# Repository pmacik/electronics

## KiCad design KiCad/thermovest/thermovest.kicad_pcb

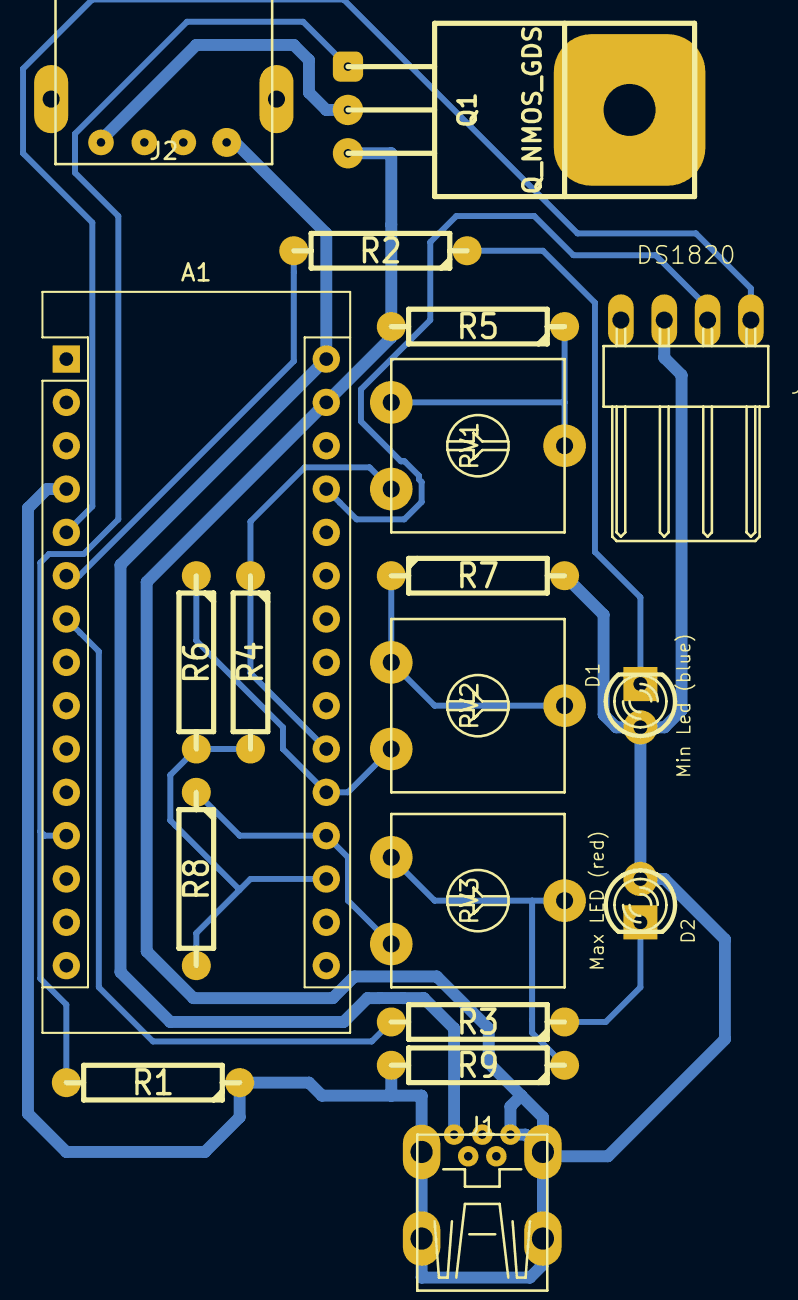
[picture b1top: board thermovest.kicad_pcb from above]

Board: 2 copper layers, 19 parts (0 on the bottom side), 17 nets.

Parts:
A1: Arduino_Nano_v3.x; Arduino_Nano
D1: Min Led (blue); LED-3MM-Large-pads
D2: Max LED (red); LED-3MM-Large-pads
J1: Power In; USB-mini
J2: Thermo Out; USB-A
J3: DS1820; PINHEAD1-4-90
Q1: Q_NMOS_GDS; TO220-123
R1, R2, R3: 1k; R4_LARGE_PADS
R4, R5, R6, R7, R8, R9: 220R; R4_LARGE_PADS
RV1: Requested Temp (4k7); Trimr
RV2: Min Temp (1k); Trimr
RV3: Max Temp (1k); Trimr

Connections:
GND: A1.4, A1.29, D1.1, D2.1, J1.5, J1.6, J3.3, Q1.3, R1.1, R5.2, R7.2, R9.2
unnamed: A1.5, J3.1
unnamed: A1.6, R2.2
unnamed: A1.7, R3.2
unnamed: A1.12, Q1.1, R1.2
unnamed: A1.18, R4.2, R6.2, R8.2
unnamed: A1.19, R8.1, RV3.3
unnamed: A1.20, R6.1, RV2.3
unnamed: A1.21, R4.1, RV1.3
unnamed: A1.27, J3.2
unnamed: A1.30, J1.1, J2.1
unnamed: D1.2, R2.1
unnamed: D2.2, R3.1
unnamed: J2.4, Q1.2
unnamed: R5.1, RV1.1, RV1.2
unnamed: R7.1, RV2.1, RV2.2
unnamed: R9.1, RV3.1, RV3.2

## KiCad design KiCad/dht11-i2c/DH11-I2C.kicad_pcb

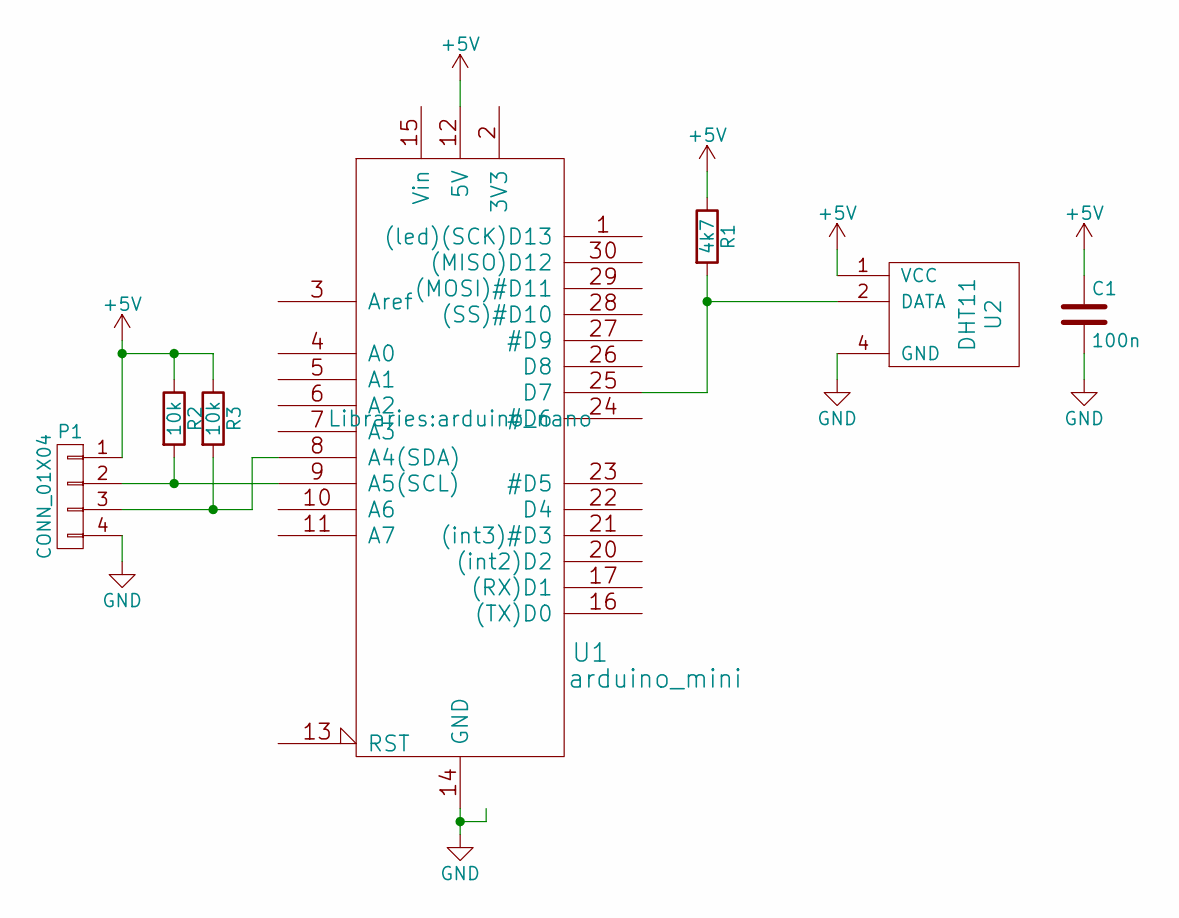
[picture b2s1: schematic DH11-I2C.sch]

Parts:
C1: 100n; C2
P1: CONN_01X04; Pin_Header_Angled_1x04
R1: 4k7; R3-LARGE_PADS
R2, R3: 10k; R3-LARGE_PADS
U1: arduino_mini; arduino_nano
U2: DHT11; Pin_Header_Angled_1x04

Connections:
+5V: C1.1, P1.1, R1.1, R2.1, R3.1, U1.12 (5V), U2.1 (VCC)
GND: C1.2, P1.4, U1.14 (GND), U1.19 (GND), U2.4 (GND)
unnamed: P1.2, R2.2, U1.9 (A5(SCL))
unnamed: P1.3, R3.2, U1.8 (A4(SDA))
unnamed: R1.2, U1.25 (D7), U2.2 (DATA)

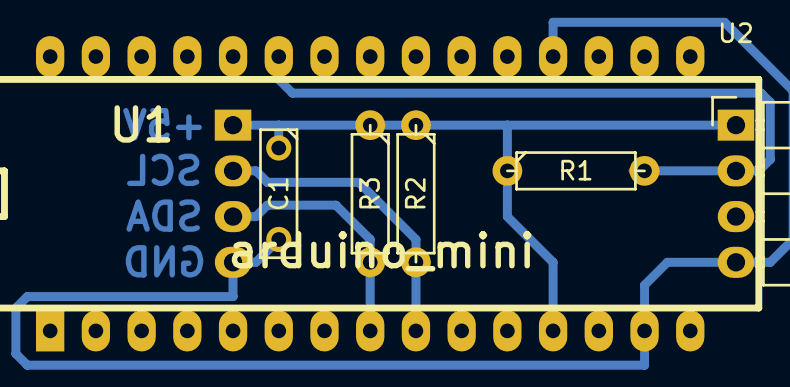
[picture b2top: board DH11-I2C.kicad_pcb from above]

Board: 2 copper layers, 7 parts (1 on the bottom side), 5 nets.

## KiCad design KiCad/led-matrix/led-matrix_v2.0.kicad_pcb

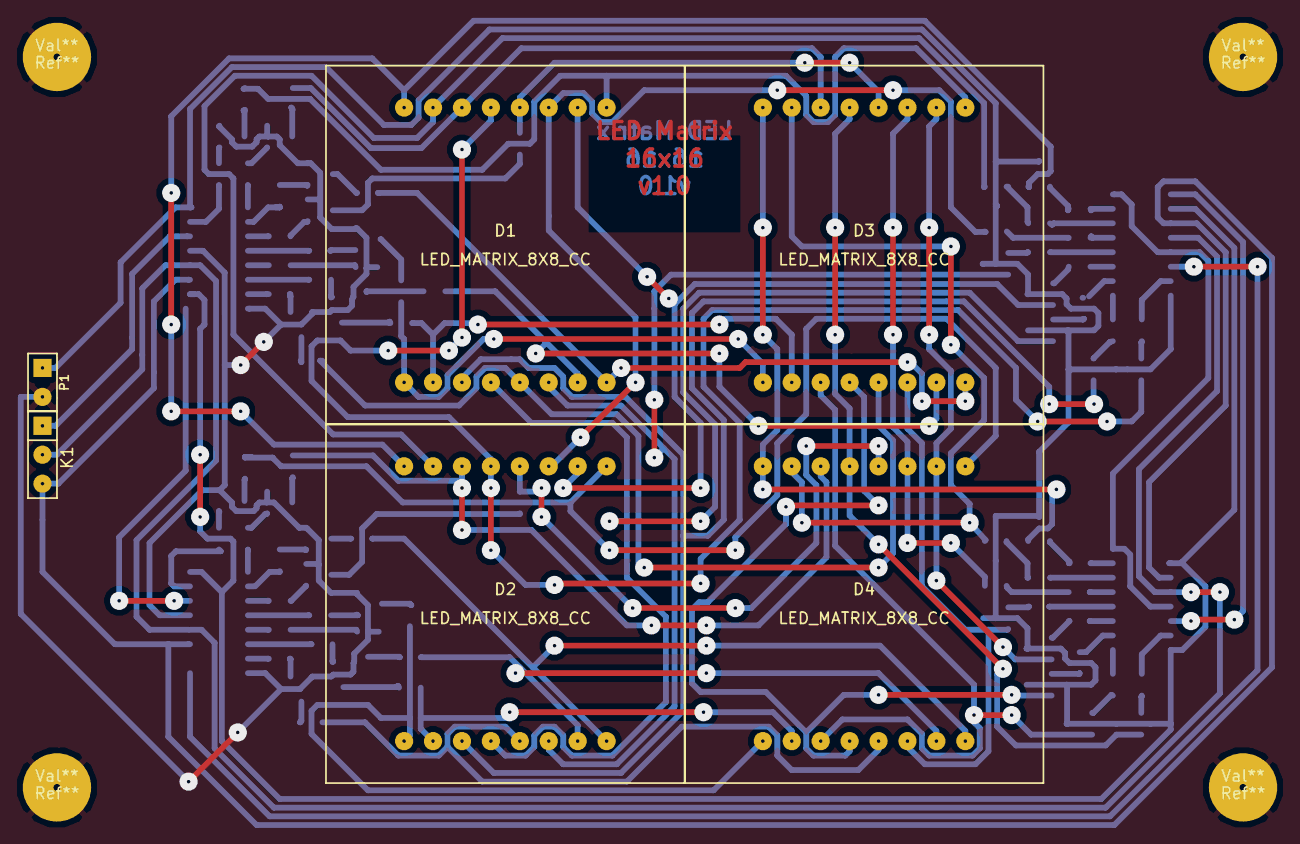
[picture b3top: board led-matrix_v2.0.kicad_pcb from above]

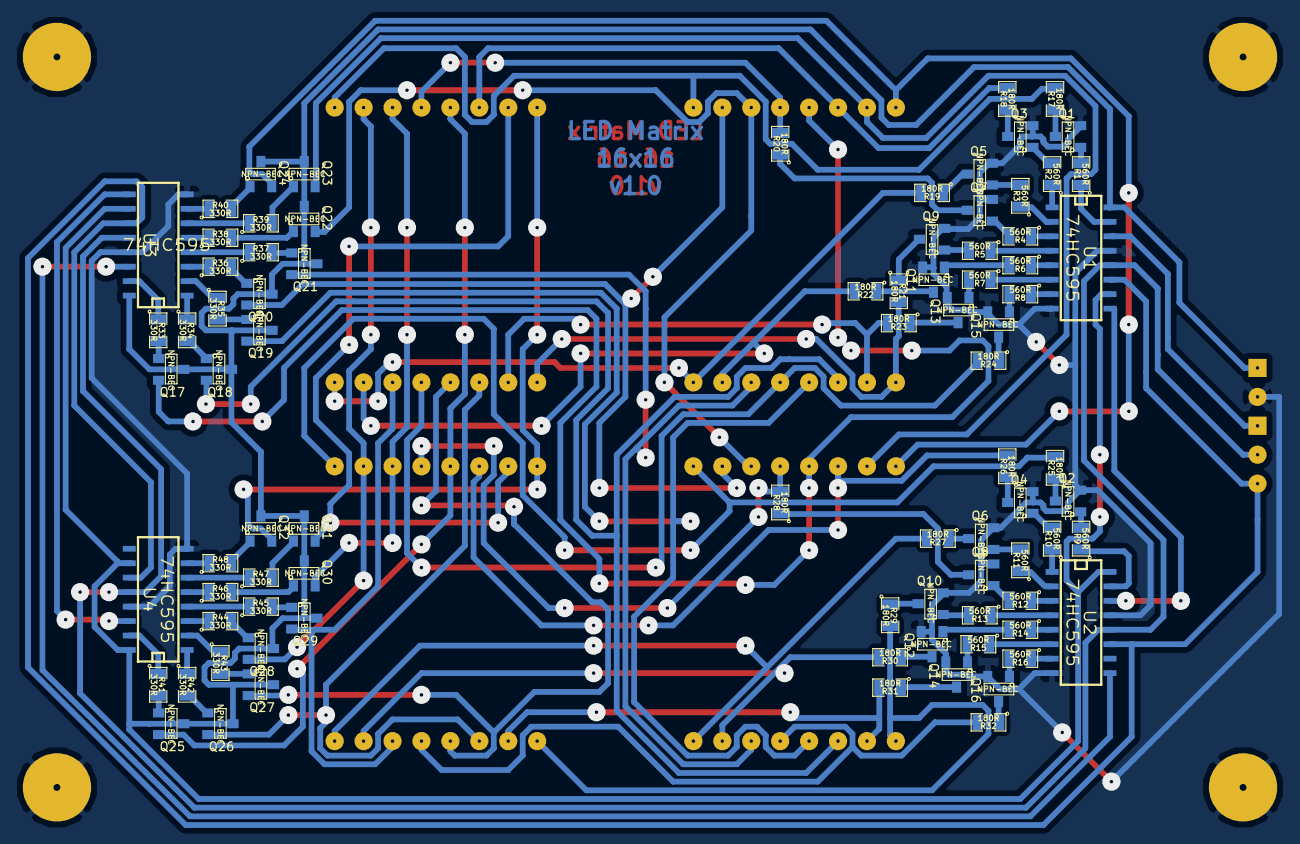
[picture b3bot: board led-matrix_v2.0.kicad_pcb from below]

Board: 2 copper layers, 94 parts (84 on the bottom side), 120 nets.

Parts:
D1, D2, D3, D4: LED_MATRIX_8X8_CC; LED_MATRIX_8x8
K1: CONN_3; PIN_ARRAY_3X1
P1: CONN_2; PIN_ARRAY_2X1
Q1, Q2, Q3, Q4, Q5, Q6, Q7, Q8, Q9, Q10, Q11, Q12, Q13, Q14, Q15, Q16, Q17, Q18, Q19, Q20, Q21, Q22, Q23, Q24, Q25, Q26, Q27, Q28, Q29, Q30, Q31, Q32: NPN-BEC; SOT23
R1, R2, R3, R4, R5, R6, R7, R8, R9, R10, R11, R12, R13, R14, R15, R16: 560R; SM0805
R17, R18, R19, R20, R21, R22, R23, R24, R25, R26, R27, R28, R29, R30, R31, R32: 180R; SM0805
R33, R34, R35, R36, R37, R38, R39, R40, R41, R42, R43, R44, R45, R46, R47, R48: 330R; SM0805
Ref**: Val**; pad
Ref**#2, Ref**#3, Ref**#4: Val**; pad
U1, U2, U3, U4: 74HC595; SO16E

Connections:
GND: P1.2, Q1.2, Q2.2, Q3.2, Q4.2, Q5.2, Q6.2, Q7.2, Q8.2, Q9.2, Q10.2, Q11.2, Q12.2, Q13.2, Q14.2, Q15.2, Q16.2, U1.8, U1.13, U2.8, U2.13, U3.8, U3.13, U4.8, U4.13
unnamed: R42.1, U4.1
unnamed: R43.1, U4.2
unnamed: R44.1, U4.3
unnamed: D3.11, D4.11, Q30.2
unnamed: Q29.1, R45.2
unnamed: Q30.1, R46.2
unnamed: R45.1, U4.4
unnamed: Q31.1, R47.2
unnamed: Q32.1, R48.2
unnamed: R14.1, U2.5
unnamed: R3.1, U1.2
unnamed: R4.1, U1.3
unnamed: R5.1, U1.4
unnamed: R6.1, U1.5
unnamed: R7.1, U1.6
unnamed: R8.1, U1.7
unnamed: R9.1, U2.15
unnamed: R10.1, U2.1
unnamed: R11.1, U2.2
unnamed: R12.1, U2.3
unnamed: R13.1, U2.4
unnamed: R2.1, U1.1
unnamed: R15.1, U2.6
unnamed: R16.1, U2.7
unnamed: Q14.1, R15.2
unnamed: R46.1, U4.5
unnamed: R47.1, U4.6
unnamed: R48.1, U4.7
unnamed: U3.9, U4.14
unnamed: R1.1, U1.15
unnamed: Q2.1, R9.2
unnamed: Q12.1, R14.2
unnamed: Q16.1, R16.2
unnamed: Q10.1, R13.2
unnamed: Q8.1, R12.2
unnamed: Q6.1, R11.2
unnamed: Q4.1, R10.2
unnamed: Q19.1, R35.2
unnamed: Q20.1, R36.2
unnamed: Q21.1, R37.2
unnamed: D1.11, D2.11, Q22.2
unnamed: Q23.1, R39.2
unnamed: Q24.1, R40.2
unnamed: Q5.1, R3.2
unnamed: Q15.1, R8.2
unnamed: Q13.1, R7.2
unnamed: Q11.1, R6.2
unnamed: Q9.1, R5.2
unnamed: Q7.1, R4.2
unnamed: Q3.1, R2.2
unnamed: Q1.1, R1.2
unnamed: Q18.1, R34.2
unnamed: K1.1, U1.14
unnamed: U2.9, U3.14
unnamed: U1.9, U2.14
unnamed: K1.2, U1.12, U2.12, U3.12, U4.12
unnamed: R33.1, U3.15
unnamed: Q22.1, R38.2
unnamed: Q17.1, R33.2
unnamed: K1.3, U1.11, U2.11, U3.11, U4.11
unnamed: R38.1, U3.5
unnamed: Q7.3, R20.1
unnamed: D2.1, D4.1, R29.2
unnamed: D2.2, D4.2, R31.2
unnamed: Q3.3, R18.1
unnamed: Q5.3, R19.1
unnamed: R34.1, U3.1
unnamed: R35.1, U3.2
unnamed: R36.1, U3.3
unnamed: R37.1, U3.4
unnamed: R39.1, U3.6
unnamed: R40.1, U3.7
unnamed: R41.1, U4.15
unnamed: Q25.1, R41.2
unnamed: Q26.1, R42.2
unnamed: Q27.1, R43.2
unnamed: Q28.1, R44.2
unnamed: D2.5, D4.5, R32.2
unnamed: D1.15, D2.15, Q23.2
unnamed: D2.14, D4.14, R26.2
unnamed: D1.16, D2.16, Q24.2
unnamed: D2.9, D4.9, R25.2
unnamed: D1.14, D3.14, R18.2
unnamed: D1.8, D3.8, R19.2
unnamed: D2.7, D4.7, R30.2
unnamed: D2.12, D4.12, R28.2
unnamed: D2.8, D4.8, R27.2
unnamed: D3.15, D4.15, Q31.2
unnamed: D3.10, D4.10, Q28.2
unnamed: D3.13, D4.13, Q25.2
unnamed: D3.16, D4.16, Q32.2
unnamed: D3.6, D4.6, Q29.2
unnamed: D1.2, D3.2, R23.2
unnamed: D1.5, D3.5, R24.2
unnamed: D3.3, D4.3, Q26.2
unnamed: D3.4, D4.4, Q27.2
unnamed: D1.13, D2.13, Q17.2
unnamed: D1.3, D2.3, Q18.2
unnamed: D1.4, D2.4, Q19.2
unnamed: D1.6, D2.6, Q21.2
unnamed: D1.10, D2.10, Q20.2
unnamed: Q8.3, R28.1
unnamed: Q6.3, R27.1
unnamed: Q4.3, R26.1
unnamed: Q2.3, R25.1
unnamed: Q15.3, R24.1
unnamed: Q13.3, R23.1
unnamed: Q11.3, R22.1
unnamed: Q9.3, R21.1
unnamed: Q1.3, R17.1
unnamed: D1.9, D3.9, R17.2
unnamed: Q16.3, R32.1
unnamed: Q14.3, R31.1
unnamed: Q12.3, R30.1
unnamed: Q10.3, R29.1
unnamed: D1.12, D3.12, R20.2
unnamed: D1.7, D3.7, R22.2
unnamed: D1.1, D3.1, R21.2
VCC: P1.1, Q17.3, Q18.3, Q19.3, Q20.3, Q21.3, Q22.3, Q23.3, Q24.3, Q25.3, Q26.3, Q27.3, Q28.3, Q29.3, Q30.3, Q31.3, Q32.3, U1.10, U1.16, U2.10, U2.16, U3.10, U3.16, U4.10, U4.16

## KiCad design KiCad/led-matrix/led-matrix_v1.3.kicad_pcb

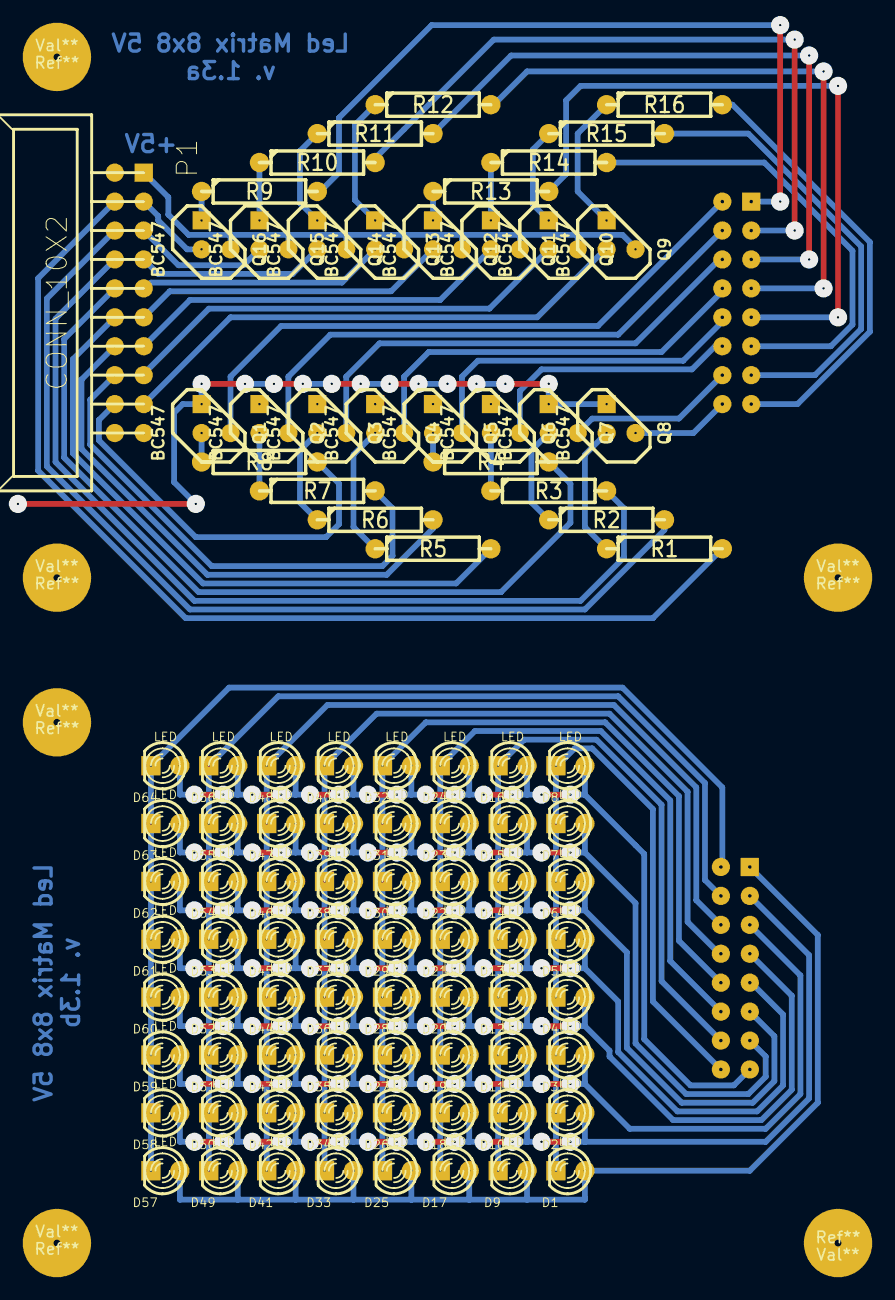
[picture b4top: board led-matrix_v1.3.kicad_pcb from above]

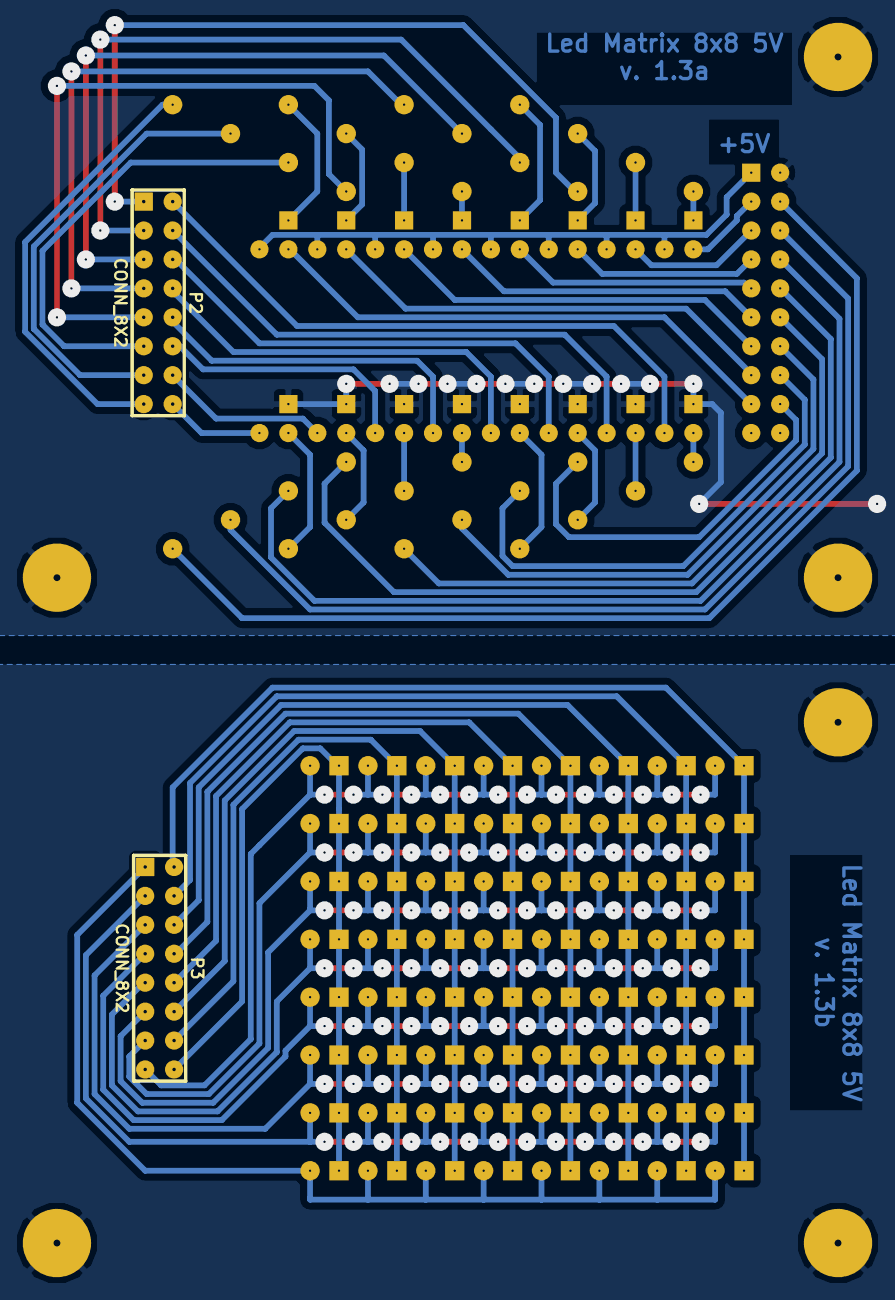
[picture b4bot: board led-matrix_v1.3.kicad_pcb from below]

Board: 2 copper layers, 105 parts (2 on the bottom side), 66 nets.

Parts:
D1, D2, D3, D4, D5, D6, D7, D8, D9, D10, D11, D12, D13, D14, D15, D16, D17, D18, D19, D20, D21, D22, D23, D24, D25, D26, D27, D28, D29, D30, D31, D32, D33, D34, D35, D36, D37, D38, D39, D40, D41, D42, D43, D44, D45, D46, D47, D48, D49, D50, D51, D52, D53, D54, D55, D56, D57, D58, D59, D60, D61, D62, D63, D64: LED; LED_3MM
P1: CONN_10X2; VASCH10x2_90
P2, P3: CONN_8X2; pin_array_8x2_large
Q1, Q2, Q3, Q4, Q5, Q6, Q7, Q8, Q9, Q10, Q11, Q12, Q13, Q14, Q15, Q16: BC547; TO92_123
R1, R2, R3, R4, R5, R6, R7, R8, R9, R10, R11, R12, R13, R14, R15, R16: R; R4_LARGE_PADS
Ref**: Val**; pad
Ref**#2, Ref**#3, Ref**#4, Ref**#5, Ref**#6: Val**; pad

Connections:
GND: P1.1, Q1.3, Q2.3, Q3.3, Q4.3, Q5.3, Q6.3, Q7.3, Q8.3
unnamed: P1.18, Q9.2
unnamed: Q13.3, R12.1
unnamed: Q12.3, R13.1
unnamed: P1.14, Q11.2
unnamed: Q11.3, R14.1
unnamed: P1.16, Q10.2
unnamed: Q10.3, R15.1
unnamed: P1.10, Q13.2
unnamed: Q9.3, R16.1
unnamed: Q16.3, R9.1
unnamed: Q15.3, R10.1
unnamed: Q14.3, R11.1
unnamed: Q5.2, R4.1
unnamed: Q6.2, R3.1
unnamed: Q7.2, R2.1
unnamed: Q8.2, R1.1
unnamed: P1.4, Q16.2
unnamed: P1.6, Q15.2
unnamed: P1.8, Q14.2
unnamed: P1.12, Q12.2
unnamed: Q2.2, R7.1
unnamed: P2.10, Q5.1
unnamed: P2.6, Q3.1
unnamed: Q3.2, R6.1
unnamed: P2.16, Q8.1
unnamed: P2.4, Q2.1
unnamed: P2.8, Q4.1
unnamed: Q4.2, R5.1
unnamed: P2.2, Q1.1
unnamed: Q1.2, R8.1
unnamed: P2.14, Q7.1
unnamed: P2.12, Q6.1
unnamed: P1.5, R2.2
unnamed: P1.7, R3.2
unnamed: P1.9, R4.2
unnamed: P1.11, R5.2
unnamed: P1.13, R6.2
unnamed: P1.15, R7.2
unnamed: P1.17, R8.2
unnamed: P1.3, R1.2
unnamed: P2.1, R9.2
unnamed: P2.3, R10.2
unnamed: P2.5, R11.2
unnamed: P2.7, R12.2
unnamed: P2.9, R13.2
unnamed: P2.11, R14.2
unnamed: P2.15, R16.2
unnamed: P2.13, R15.2
unnamed: D4.1, D12.1, D20.1, D28.1, D36.1, D44.1, D52.1, D60.1, P3.7
unnamed: D5.1, D13.1, D21.1, D29.1, D37.1, D45.1, D53.1, D61.1, P3.9
unnamed: D7.1, D15.1, D23.1, D31.1, D39.1, D47.1, D55.1, D63.1, P3.13
unnamed: D1.2, D2.2, D3.2, D4.2, D5.2, D6.2, D7.2, D8.2, P3.16
unnamed: D17.2, D18.2, D19.2, D20.2, D21.2, D22.2, D23.2, D24.2, P3.12
unnamed: D9.2, D10.2, D11.2, D12.2, D13.2, D14.2, D15.2, D16.2, P3.14
unnamed: D1.1, D9.1, D17.1, D25.1, D33.1, D41.1, D49.1, D57.1, P3.1
unnamed: D3.1, D11.1, D19.1, D27.1, D35.1, D43.1, D51.1, D59.1, P3.5
unnamed: D2.1, D10.1, D18.1, D26.1, D34.1, D42.1, D50.1, D58.1, P3.3
unnamed: D57.2, D58.2, D59.2, D60.2, D61.2, D62.2, D63.2, D64.2, P3.2
unnamed: D41.2, D42.2, D43.2, D44.2, D45.2, D46.2, D47.2, D48.2, P3.6
unnamed: D49.2, D50.2, D51.2, D52.2, D53.2, D54.2, D55.2, D56.2, P3.4
unnamed: D25.2, D26.2, D27.2, D28.2, D29.2, D30.2, D31.2, D32.2, P3.10
unnamed: D8.1, D16.1, D24.1, D32.1, D40.1, D48.1, D56.1, D64.1, P3.15
unnamed: D33.2, D34.2, D35.2, D36.2, D37.2, D38.2, D39.2, D40.2, P3.8
unnamed: D6.1, D14.1, D22.1, D30.1, D38.1, D46.1, D54.1, D62.1, P3.11
VCC: P1.2, Q9.1, Q10.1, Q11.1, Q12.1, Q13.1, Q14.1, Q15.1, Q16.1

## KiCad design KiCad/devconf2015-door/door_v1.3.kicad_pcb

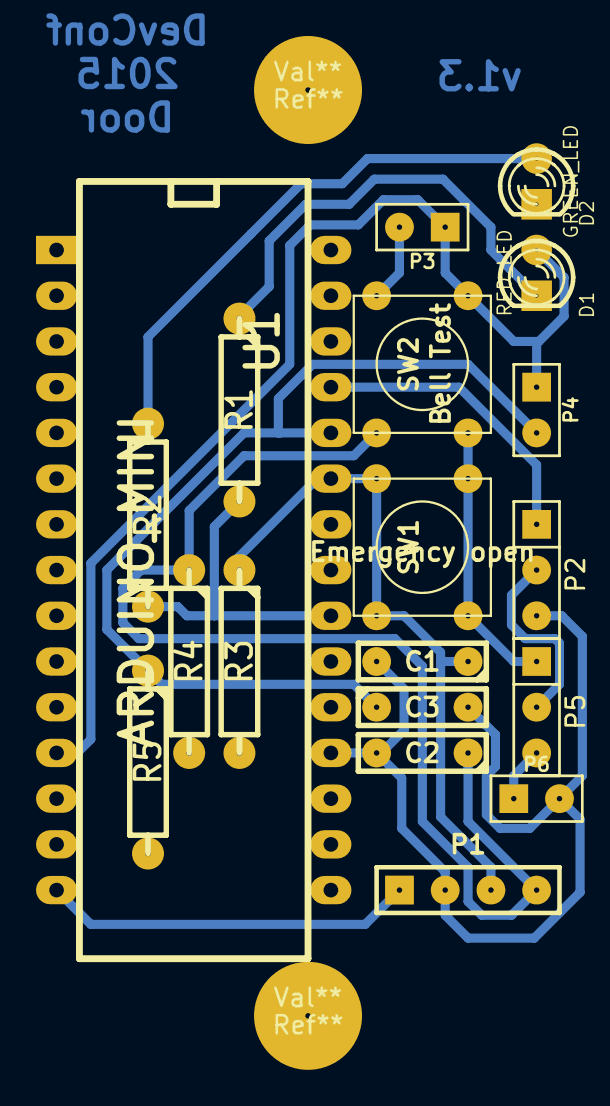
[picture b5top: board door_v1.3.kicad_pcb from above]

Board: 2 copper layers, 21 parts (0 on the bottom side), 12 nets.

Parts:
C1, C2, C3: 100nF; C2
D1: RED_LED; LED_3MM
D2: GREEN_LED; LED_3MM
P1: Cubieboard; PIN_ARRAY_4x1
P2: Servo; PIN_ARRAY_3X1
P3: Bell; PIN_ARRAY_2X1
P4: Door Open; PIN_ARRAY_2X1
P5: Servo PWR Jmpr; PIN_ARRAY_3X1
P6: Servo Ext PWR; PIN_ARRAY_2X1
R1, R2: R; R4-LARGE_PADS
R3, R4, R5: 1M; R4-LARGE_PADS
Ref**: Val**; pad
Ref**#2: Val**; pad
SW1: Emergency open; SW_PUSH_SMALL
SW2: Bell Test; SW_PUSH_SMALL
U1: ARDUINO_MINI; arduino_mini

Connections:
+5V: D1.1, P3.1, P4.1, P5.1, SW1.2, SW2.2, U1.12
GND: C1.2, C2.2, C3.2, D2.2, P1.2, P2.3, P6.2, R3.2, R4.2, R5.2, U1.14, U1.19
unnamed: R1.2, R2.1, U1.22
unnamed: D2.1, R2.2
unnamed: D1.2, R1.1
unnamed: P2.1, U1.27
unnamed: P5.3, P6.1
unnamed: P2.2, P5.2
unnamed: C3.1, P4.2, R5.1, U1.26
unnamed: C1.1, P1.3, R3.1, SW1.1, U1.25
unnamed: C2.1, P1.4, P3.2, R4.1, SW2.1
VCC: P1.1, U1.15

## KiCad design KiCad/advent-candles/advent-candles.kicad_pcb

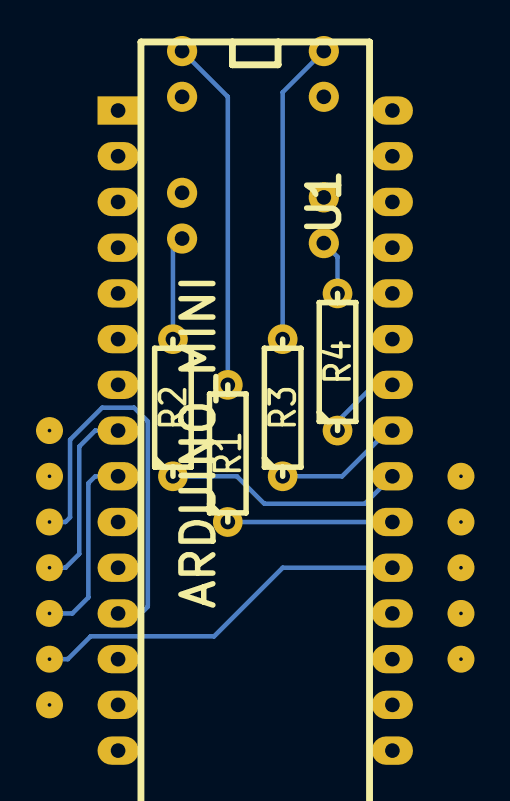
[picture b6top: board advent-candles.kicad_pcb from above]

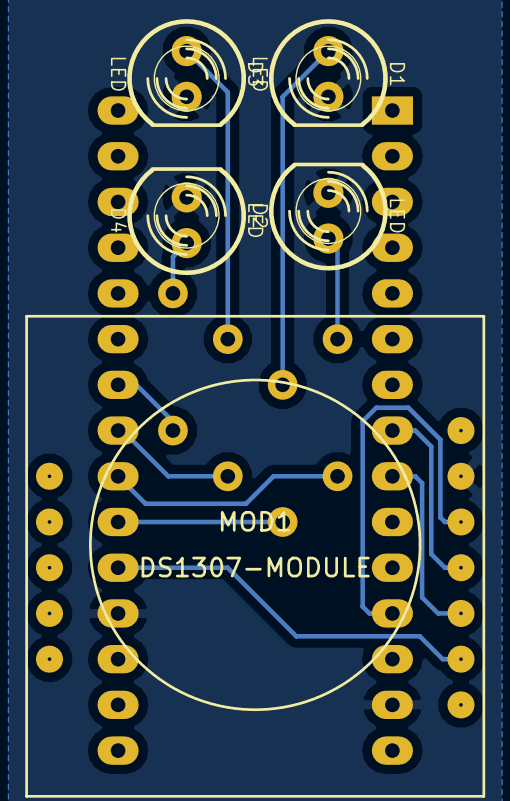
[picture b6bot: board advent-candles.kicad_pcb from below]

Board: 2 copper layers, 10 parts (5 on the bottom side), 13 nets.

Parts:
D1, D2, D3, D4: LED; LED-5MM
MOD1: DS1307-MODULE
R1, R2, R3, R4: R; R3-LARGE_PADS
U1: ARDUINO_MINI; arduino_mini

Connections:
GND: D1.2, D2.2, D3.2, D4.2, MOD1.6, U1.14, U1.19
unnamed: D3.1, R3.2
unnamed: D2.1, R2.2
unnamed: D1.1, R1.2
unnamed: D4.1, R4.2
unnamed: MOD1.5, U1.12
unnamed: MOD1.4, U1.8
unnamed: R4.1, U1.24
unnamed: R3.1, U1.23
unnamed: R2.1, U1.22
unnamed: R1.1, U1.21
unnamed: MOD1.3, U1.9
unnamed: MOD1.2, U1.20

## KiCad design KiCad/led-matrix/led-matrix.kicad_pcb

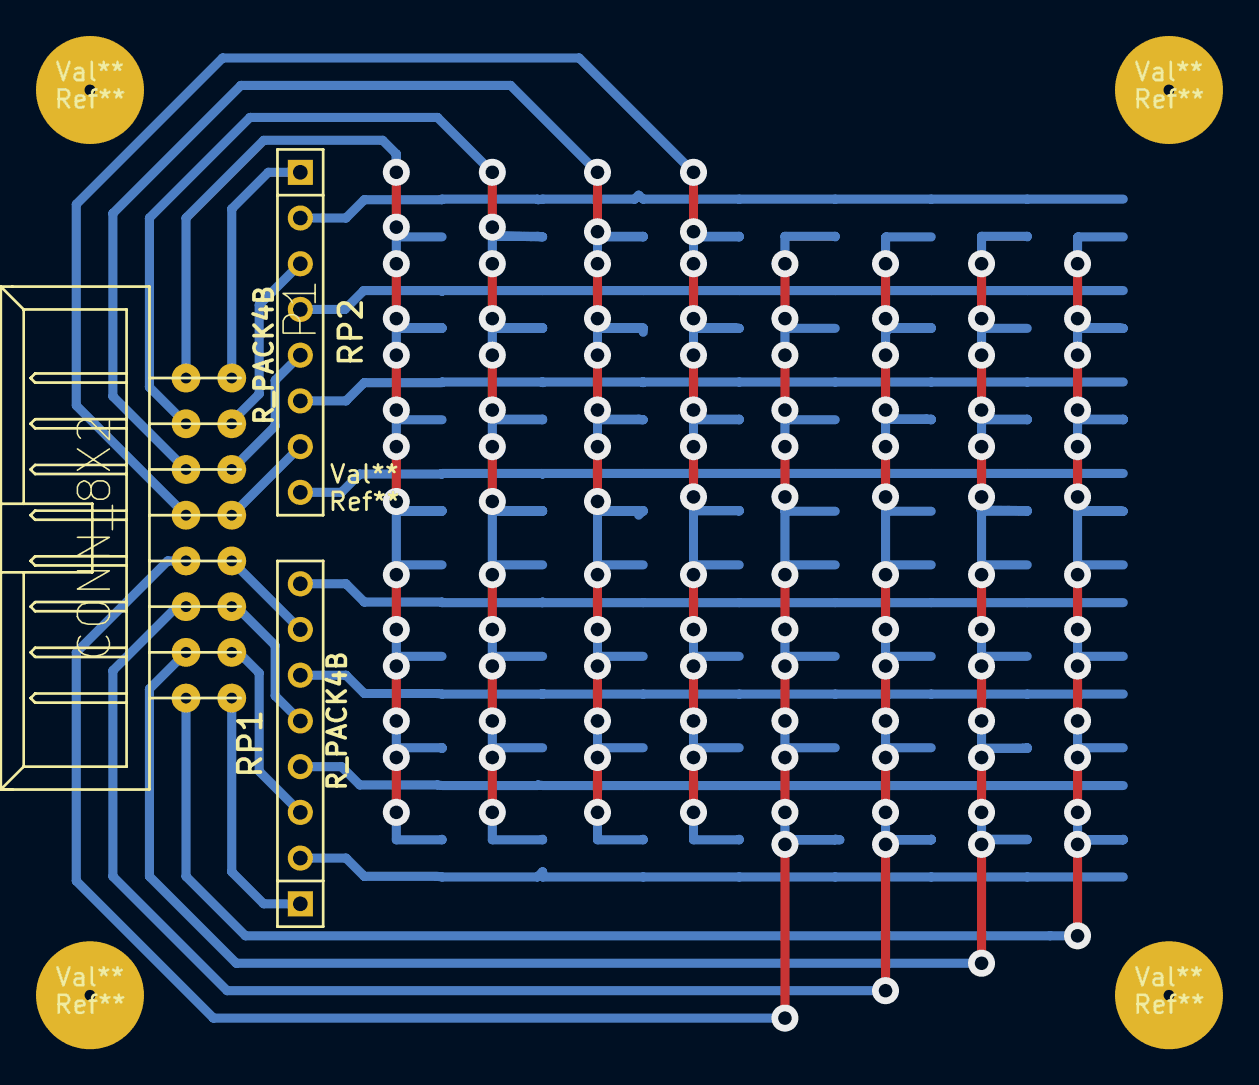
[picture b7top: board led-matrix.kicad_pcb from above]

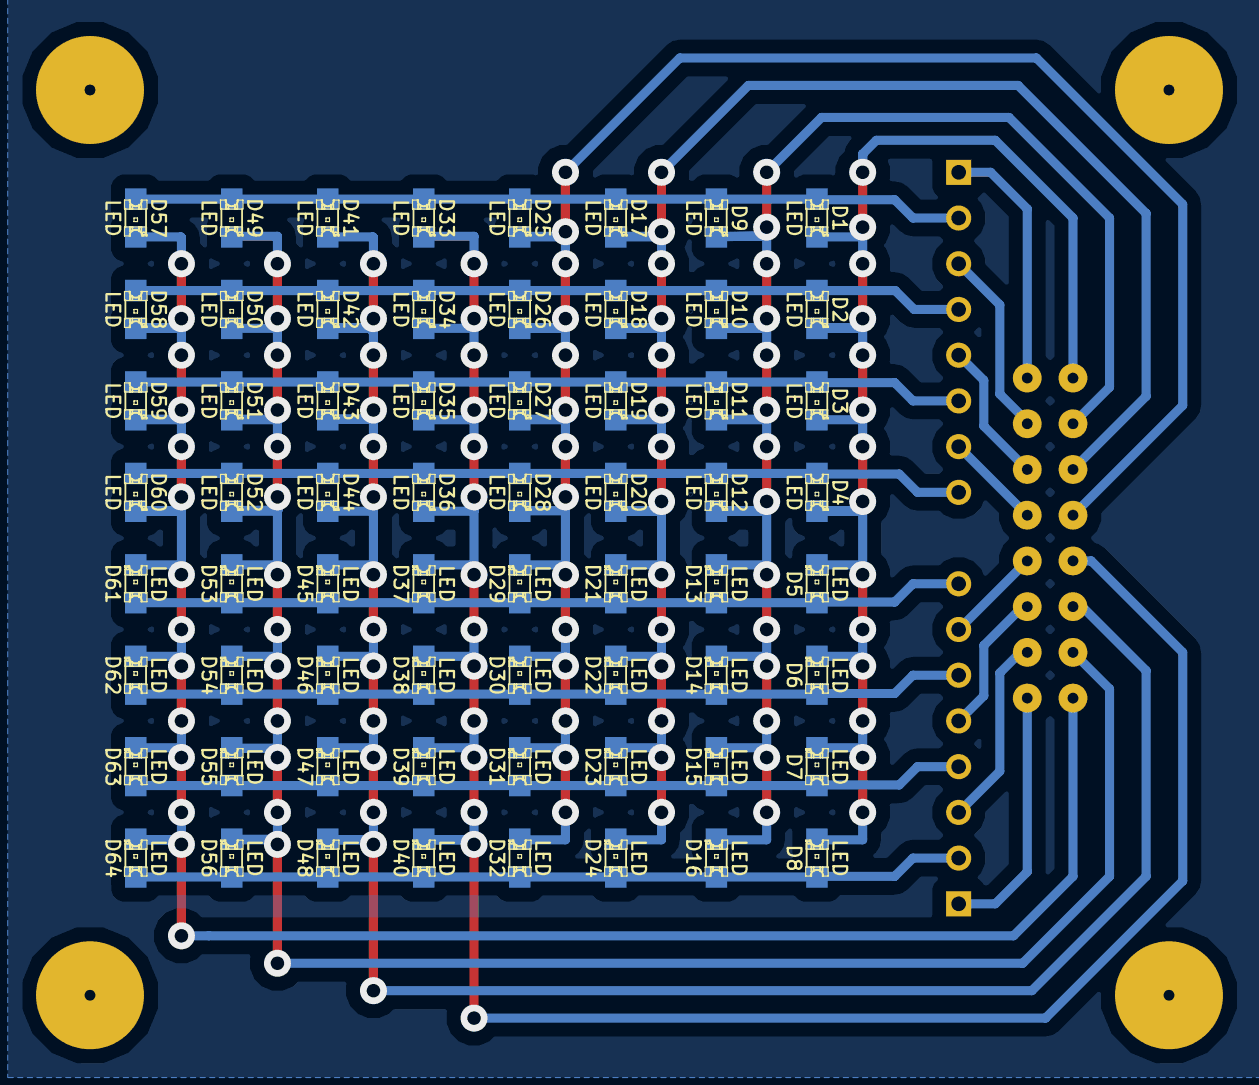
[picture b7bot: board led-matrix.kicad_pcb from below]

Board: 2 copper layers, 72 parts (64 on the bottom side), 24 nets.

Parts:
D1, D2, D3, D4, D5, D6, D7, D8, D9, D10, D11, D12, D13, D14, D15, D16, D17, D18, D19, D20, D21, D22, D23, D24, D25, D26, D27, D28, D29, D30, D31, D32, D33, D34, D35, D36, D37, D38, D39, D40, D41, D42, D43, D44, D45, D46, D47, D48, D49, D50, D51, D52, D53, D54, D55, D56, D57, D58, D59, D60, D61, D62, D63, D64: LED; LED-0805
P1: CONN_8X2; VASCH8x2-90
RP1, RP2: R_PACK4B; r_pack4B
Ref**: Val**; pad
Ref**#2, Ref**#3, Ref**#4, Ref**#5: Val**; pad

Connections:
unnamed: D17.2, D18.2, D19.2, D20.2, D21.2, D22.2, D23.2, D24.2, P1.5
unnamed: D9.2, D10.2, D11.2, D12.2, D13.2, D14.2, D15.2, D16.2, P1.3
unnamed: D1.2, D2.2, D3.2, D4.2, D5.2, D6.2, D7.2, D8.2, P1.1
unnamed: D8.1, D16.1, D24.1, D32.1, D40.1, D48.1, D56.1, D64.1, RP1.2
unnamed: P1.10, RP1.7
unnamed: P1.12, RP1.5
unnamed: P1.14, RP1.3
unnamed: P1.16, RP1.1
unnamed: P1.8, RP2.7
unnamed: P1.6, RP2.5
unnamed: P1.4, RP2.3
unnamed: P1.2, RP2.1
unnamed: D25.2, D26.2, D27.2, D28.2, D29.2, D30.2, D31.2, D32.2, P1.7
unnamed: D57.2, D58.2, D59.2, D60.2, D61.2, D62.2, D63.2, D64.2, P1.15
unnamed: D49.2, D50.2, D51.2, D52.2, D53.2, D54.2, D55.2, D56.2, P1.13
unnamed: D41.2, D42.2, D43.2, D44.2, D45.2, D46.2, D47.2, D48.2, P1.11
unnamed: D33.2, D34.2, D35.2, D36.2, D37.2, D38.2, D39.2, D40.2, P1.9
unnamed: D1.1, D9.1, D17.1, D25.1, D33.1, D41.1, D49.1, D57.1, RP2.2
unnamed: D7.1, D15.1, D23.1, D31.1, D39.1, D47.1, D55.1, D63.1, RP1.4
unnamed: D2.1, D10.1, D18.1, D26.1, D34.1, D42.1, D50.1, D58.1, RP2.4
unnamed: D4.1, D12.1, D20.1, D28.1, D36.1, D44.1, D52.1, D60.1, RP2.8
unnamed: D6.1, D14.1, D22.1, D30.1, D38.1, D46.1, D54.1, D62.1, RP1.6
unnamed: D5.1, D13.1, D21.1, D29.1, D37.1, D45.1, D53.1, D61.1, RP1.8
unnamed: D3.1, D11.1, D19.1, D27.1, D35.1, D43.1, D51.1, D59.1, RP2.6

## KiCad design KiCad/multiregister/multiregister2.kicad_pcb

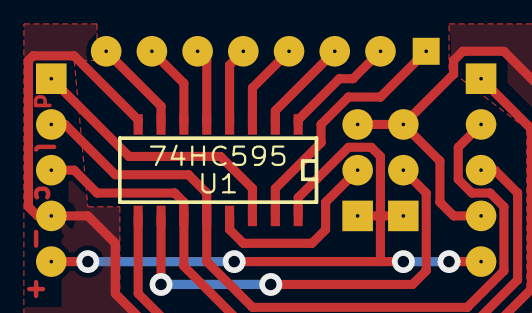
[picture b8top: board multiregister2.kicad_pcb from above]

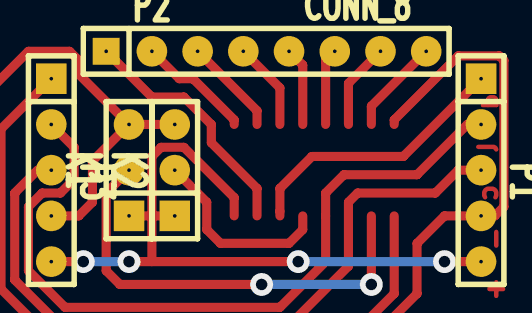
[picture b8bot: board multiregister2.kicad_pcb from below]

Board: 2 copper layers, 6 parts (5 on the bottom side), 16 nets.

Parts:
K1, K2: CONN_3; SIL-3
P1, P3: CONN_5; SIL-5
P2: CONN_8; SIL-8
U1: 74HC595; SO16E

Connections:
GND: K1.3, K2.3, P1.4, P3.4, U1.8
unnamed: K2.2, U1.13
unnamed: K1.2, U1.10
unnamed: P1.2, P3.2, U1.12
unnamed: P1.3, P3.3, U1.11
unnamed: P1.1, U1.14
unnamed: P2.8, U1.7
unnamed: P2.7, U1.6
unnamed: P2.6, U1.5
unnamed: P2.5, U1.4
unnamed: P2.4, U1.3
unnamed: P2.3, U1.2
unnamed: P2.2, U1.1
unnamed: P2.1, U1.15
unnamed: P3.1, U1.9
VCC: K1.1, K2.1, P1.5, P3.5, U1.16

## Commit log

2014-12-19 multiregister: cases moved to the right side of the pcb
2014-12-19 advent-candles: removed useless GND wires
2014-12-21 advent-candles: created alternative, one-sided and bigger PCB version (v1.1)
2014-12-22 advent-candles: updated the PCB with pods for screws
2014-12-22 advent-candles: Added the Arduino source code.
2015-01-24 devconf2015-door: Added PCB and Arduino code for DevConf2015 IoT Demo Door
2015-01-24 led-matrix: added Arduino code and alternative PCB
2015-01-24 led-matrix: updated Arduino code version
2015-02-20 [led-matrix] Created 16x16 matrix marked as v2.
2015-04-02 [KiCad-libs] Updated sewer module library with several new modules.
2016-02-06 [dht11-i2c] DHT11 over I2C added
2016-02-06 Rename dht11-i2c.c to dht11-i2c.ino
2019-03-07 thermovest: Add KiCAD and Arduino sources
